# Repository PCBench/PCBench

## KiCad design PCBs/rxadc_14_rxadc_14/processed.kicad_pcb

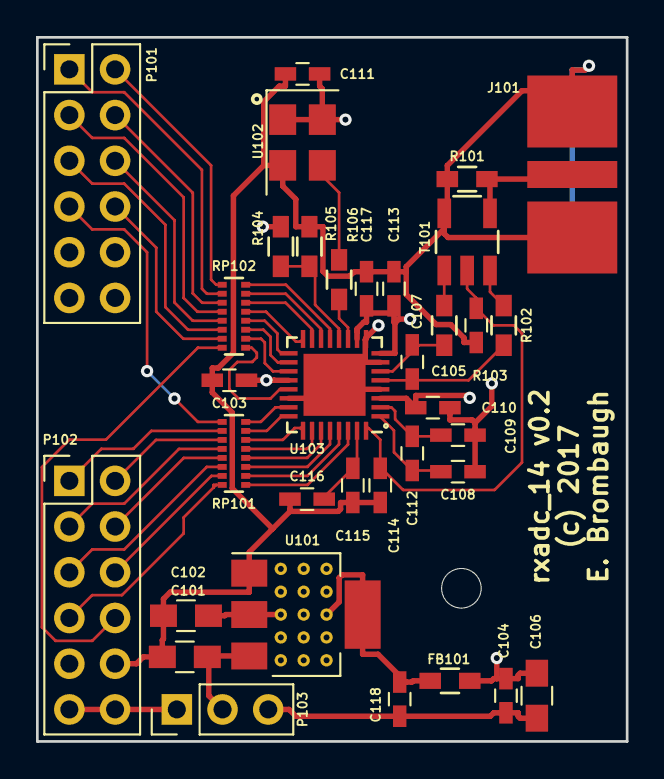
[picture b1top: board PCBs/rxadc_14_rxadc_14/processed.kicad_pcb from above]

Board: 4 copper layers, 32.8 x 39.1 mm, 35 parts (0 on the bottom side), 49 nets.

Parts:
C101, C102, C106: 10uf; C_0805_HandSoldering
C103, C104, C105, C108, C109, C110, C111, C113, C114, C115, C117, C118: 0.1uf; C_0603_HandSoldering
C107: 18pf; C_0603_HandSoldering
C112, C116: 1uf; C_0603_HandSoldering
FB101: FILTER; R_0603_HandSoldering
J101: SMA; SMA_END
P101, P102: CONN_02X06; Pin_Header_Straight_2x06_Pitch2.54mm
P103: CONN_01X03; Pin_Header_Straight_1x03_Pitch2.54mm
R101, R106: 50; R_0603_HandSoldering
R102, R103: 20; R_0603_HandSoldering
R104: 4k7; R_0603_HandSoldering
R105: 10k; R_0603_HandSoldering
RP101, RP102: 100; R_Array_EXB2HV
T101: TRANSFO4; Pulse_SMD_Balun
U101: LD1117S33CTR; SOT-223
U102: ASFL1-80.000MHZ-EC-T; Crystal_SMD_Abracon_ASFL1-4pin_5.0x3.2mm
U103: ADC14C105; QFN-32-1EP_5x5mm_Pitch0.5mm_extended_pad

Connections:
+3.3VADC: C104.1, C106.1, C110.1, C113.1, C117.1, FB101.2, R104.1, U103.3, U103.8, U103.10
+3V3: C102.1, C103.1, C111.1, C118.2, FB101.1, U101.2, U101.4, U102.1, U102.4, U103.20
+5V: C101.1, P103.2, U101.3
GND: C101.2, C102.2, C103.2, C104.2, C105.1, C106.2, C108.1, C109.1, C110.2, C111.2, C113.2, C114.1, C115.1, C116.1, C117.2, C118.1, J101.2, P101.9, P101.10, P102.9, P102.10, P103.3, R101.1, R105.2, T101.5, U101.1, U102.2, U103.4, U103.7, U103.9, U103.22, U103.33
unnamed: C105.2, C114.2, T101.2, U103.32
unnamed: C107.1, R102.2, U103.5
unnamed: C107.2, R103.2, U103.6
unnamed: C108.2, C112.1, U103.1
unnamed: C109.2, C112.2, U103.2
unnamed: C115.2, C116.2, U103.31
unnamed: J101.1, R101.2, T101.4
unnamed: P101.1, RP102.10
unnamed: P101.2, RP102.9
unnamed: P101.3, RP102.12
unnamed: P101.4, RP102.11
unnamed: P101.5, RP102.14
unnamed: P101.6, RP102.13
unnamed: P101.7, RP101.9
unnamed: P101.8, RP102.15
unnamed: P102.1, RP101.10
unnamed: P102.2, RP101.11
unnamed: P102.3, RP101.12
unnamed: P102.4, RP101.13
unnamed: P102.5, RP101.14
unnamed: P102.6, RP101.15
unnamed: P102.7, RP101.16
unnamed: P102.8, RP102.16
unnamed: P102.11, P102.12, P103.1
unnamed: R102.1, T101.3
unnamed: R103.1, T101.1
unnamed: R104.2, R105.1, U103.12
unnamed: R106.1, U103.11
unnamed: R106.2, U102.3
unnamed: RP101.1, U103.30
unnamed: RP101.2, U103.29
unnamed: RP101.3, U103.28
unnamed: RP101.4, U103.27
unnamed: RP101.5, U103.26
unnamed: RP101.6, U103.25
unnamed: RP101.7, U103.24
unnamed: RP101.8, U103.23
unnamed: RP102.1, U103.21
unnamed: RP102.2, U103.19
unnamed: RP102.3, U103.18
unnamed: RP102.4, U103.17
unnamed: RP102.5, U103.16
unnamed: RP102.6, U103.15
unnamed: RP102.7, U103.14
unnamed: RP102.8, U103.13

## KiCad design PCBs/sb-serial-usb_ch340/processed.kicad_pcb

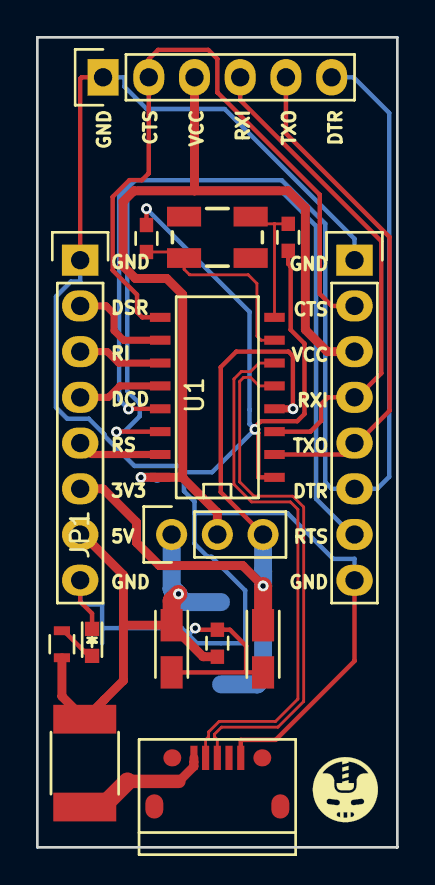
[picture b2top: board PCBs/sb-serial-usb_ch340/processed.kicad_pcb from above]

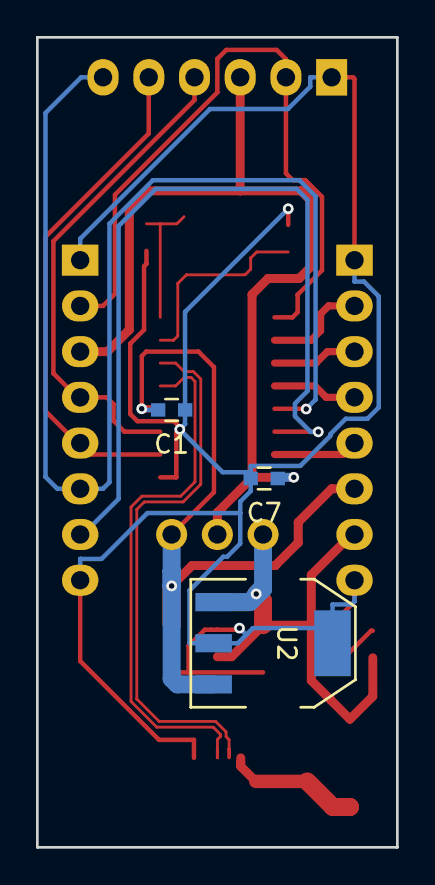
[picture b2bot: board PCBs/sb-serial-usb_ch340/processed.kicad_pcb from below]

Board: 2 copper layers, 20.0 x 45.0 mm, 18 parts (3 on the bottom side), 19 nets.

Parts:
C1: 10n; C_0603
C2, C3: 22p; C_0603
C4, C6: 10u 6V TANT; TantalC_SizeA_EIA-3216_Reflow
C5: 1u; C_0603
C7: 100n; C_0603
D1: BLUE; LED_0603
F1: 1.5A; R_1812
JP1: JUMPER3; Pin_Header_Straight_1x03
P1: CONN_01X06; Pin_Header_Straight_1x06
P2, P3: CONN_01X08; Pin_Header_Straight_1x08
P4: MINI-USB; USB_Micro-B
R1: 1K; R_0603
U1: CH340G; SO-16-N
U2: LDO MIC39100 3.3V; SOT-223
Y1: 12Mhz; CRYSTAL-SMD-5X3

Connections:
+5V: C4.1, C5.1, F1.2, JP1.1, P3.7, R1.2, U2.1
CTS: P1.2, P2.2, U1.9
D+: P4.3, U1.5
D-: P4.2, U1.6
DCD: P3.4, U1.12
DSR: P3.2, U1.10
DTR: P1.6, P2.6, U1.13
GND: C1.1, C2.2, C3.2, C4.2, C5.2, C6.2, C7.2, D1.1, P1.1, P2.1, P2.8, P3.1, P3.8, P4.5, U1.1, U2.2, U2.4
unnamed: C2.1, U1.7, Y1.1
unnamed: C3.1, U1.8, Y1.2
unnamed: D1.2, R1.1
unnamed: F1.1, P4.1
RI: P3.3, U1.11
RS232: P3.5, U1.15
RTS: P2.7, U1.14
RXI: P1.4, P2.4, U1.3
TXO: P1.5, P2.5, U1.2
V3: C1.2, C6.1, JP1.3, P3.6, U1.4, U2.3
VCC: C7.1, JP1.2, P1.3, P2.3, U1.16

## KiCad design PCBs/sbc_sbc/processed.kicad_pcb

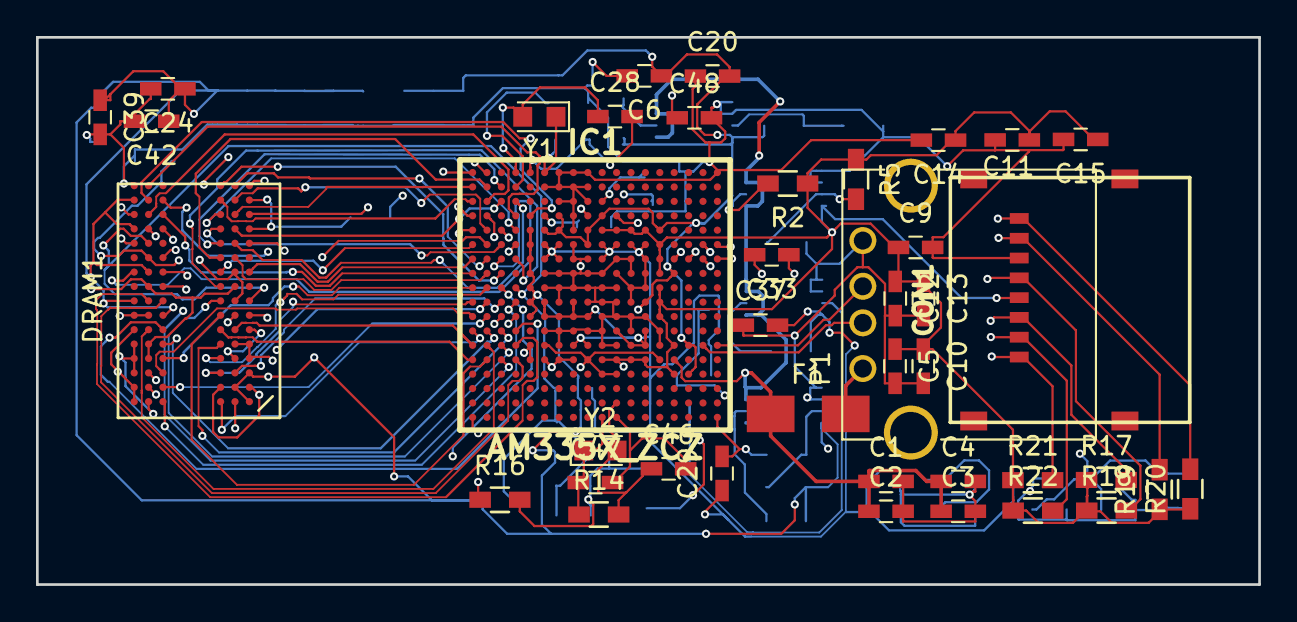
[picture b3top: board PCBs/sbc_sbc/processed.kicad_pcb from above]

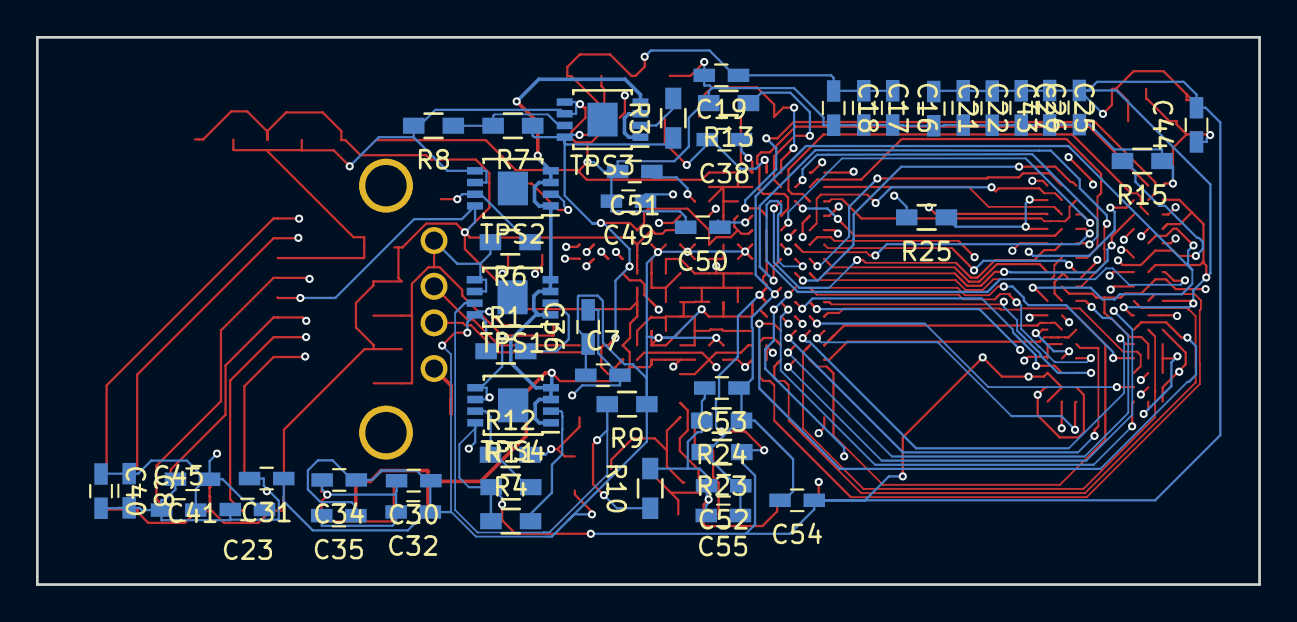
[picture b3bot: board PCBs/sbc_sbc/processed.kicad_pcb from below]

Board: 4 copper layers, 67.9 x 30.4 mm, 91 parts (50 on the bottom side), 85 nets.

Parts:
C1, C2, C3, C4, C15, C20, C26, C27, C37, C44, C45: 10uF; C_0603_HandSoldering
C5, C6, C7, C8: 22uF; C_0603_HandSoldering
C9, C10, C11, C12, C13, C14, C16, C17, C18, C19, C29, C30, C31, C32, C33, C34, C35, C36: 10nF; C_0603_HandSoldering
C21, C22, C23, C24, C25, C39, C40, C41, C42, C43, C48, C49, C50, C51: 1uF; C_0603_HandSoldering
C28, C38: 25pF; C_0603_HandSoldering
C46, C47: 24pF; C_0603_HandSoldering
C52, C53, C54, C55: 0.1uF; C_0603_HandSoldering
CON1: Micro_SD_Card; MICRO_SD_HINGE_AMP
DRAM1: DRAM-IS43TR16128B-125KBL; BGA-96_pitch0.8mm_dia0.4mm
F1: Polyfuse; Fuse_SMD1206_HandSoldering
IC1: AM335X_ZCZ; bga-csg324
P1: USB_A
R1, R2, R3, R4: 499K; R_0603_HandSoldering
R5: 250K; R_0603_HandSoldering
R6, R8, R10, R12: 80K; R_0603_HandSoldering
R7: 100K; R_0603_HandSoldering
R9: 30K; R_0603_HandSoldering
R11: 70K; R_0603_HandSoldering
R13, R17, R18, R19, R20, R21, R22, R25: 10K; R_0603_HandSoldering
R14: 1M; R_0603_HandSoldering
R15: 240; R_0603_HandSoldering
R16: 49.9; R_0603_HandSoldering
R23, R24: 1K; R_0603_HandSoldering
TPS1, TPS2, TPS3, TPS4: TPS82084; MSOP-8-1EP_3x3mm_Pitch0.65mm
Y1: 32.768KHz; Crystal_SMD_2012-2pin_2.0x1.2mm_HandSoldering
Y2: 24MHz; Crystal_SMD_2012-2pin_2.0x1.2mm_HandSoldering

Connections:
1.1V: C7.1, C29.1, C30.1, C31.1, C32.1, C33.1, C34.1, C35.1, C36.1, C37.2, IC1.A2, IC1.F6, IC1.F7, IC1.F10, IC1.F11, IC1.F12, IC1.F13, IC1.G6, IC1.G7, IC1.G10, IC1.G13, IC1.H11, IC1.H13, IC1.J12, IC1.J13, IC1.K6, IC1.K8, IC1.K12, IC1.L6, IC1.L7, IC1.L8, IC1.L9, IC1.M11, IC1.M13, IC1.N8, IC1.N9, IC1.N12, IC1.N13, R1.1, R9.1, TPS1.8
1.8V: C6.1, C16.1, C17.1, C18.1, C19.1, C20.2, IC1.D7, IC1.D10, IC1.E6, IC1.E7, IC1.E9, IC1.E14, IC1.F9, IC1.H15, IC1.K13, IC1.N6, IC1.N16, IC1.P9, IC1.P14, IC1.R10, IC1.R11, IC1.R16, R3.1, R7.1, TPS3.8
+1.5V: C8.1, C21.1, C22.1, C23.1, C24.1, C25.1, C26.1, C27.2, C39.1, C40.1, C41.1, C42.1, C43.1, C44.2, C45.2, C54.1, DRAM1.A1, DRAM1.A8, DRAM1.B2, DRAM1.C1, DRAM1.C9, DRAM1.D2, DRAM1.D9, DRAM1.E9, DRAM1.F1, DRAM1.G7, DRAM1.H2, DRAM1.H9, DRAM1.K2, DRAM1.K8, DRAM1.N1, DRAM1.N9, DRAM1.R1, DRAM1.R9, IC1.E5, IC1.F5, IC1.G5, IC1.H5, IC1.J5, IC1.K5, IC1.L5, R4.1, R11.1, R23.1, R25.1, TPS4.8
+3V3: C5.1, C9.1, C10.1, C11.1, C12.1, C13.1, C14.1, C15.1, CON1.4, IC1.E10, IC1.E11, IC1.E12, IC1.E13, IC1.F14, IC1.G14, IC1.H14, IC1.J14, IC1.K14, IC1.L14, IC1.N5, IC1.N15, IC1.P5, IC1.P6, IC1.P7, IC1.P8, IC1.P10, IC1.P11, IC1.P12, IC1.P13, IC1.R15, R2.1, R5.1, R17.1, R18.1, R19.1, R20.1, R21.1, R22.1, TPS2.8
+5V: C1.1, C2.1, C3.1, C4.1, F1.1, IC1.P15, TPS1.1, TPS1.3, TPS1.4, TPS2.1, TPS2.3, TPS2.4, TPS3.1, TPS3.3, TPS3.4, TPS4.1, TPS4.3, TPS4.4
/1.1FB: R9.2, R10.1, TPS1.7
/1.5FB: R11.2, R12.1, TPS4.7
/1.8FB: R7.2, R8.1, TPS3.7
/3.3FB: R5.2, R6.1, TPS2.7
/DDR_A0: DRAM1.N3, IC1.F3
/DDR_A1: DRAM1.P7, IC1.H1
/DDR_A2: DRAM1.P3, IC1.E4
/DDR_A3: DRAM1.N2, IC1.C3
/DDR_A4: DRAM1.P8, IC1.C2
/DDR_A5: DRAM1.P2, IC1.B1
/DDR_A6: DRAM1.R8, IC1.D5
/DDR_A7: DRAM1.R2, IC1.E2
/DDR_A8: DRAM1.T8, IC1.D4
/DDR_A9: DRAM1.R3, IC1.C1
/DDR_A10: DRAM1.L7, IC1.F4
/DDR_A11: DRAM1.R7, IC1.F2
/DDR_A12: DRAM1.N7, IC1.E3
/DDR_A13: DRAM1.T3, IC1.H3
/DDR_BA0: DRAM1.M2, IC1.C4
/DDR_BA1: DRAM1.N8, IC1.E1
/DDR_BA2: DRAM1.M3, IC1.B3
/DDR_CASn: DRAM1.K3, IC1.F1
/DDR_CK: DRAM1.J7, IC1.D2
/DDR_CKE: DRAM1.K9, IC1.G3
/DDR_CKn: DRAM1.K7, IC1.D1
/DDR_CSn0: DRAM1.L2, IC1.H2
/DDR_D0: DRAM1.E3, IC1.M3
/DDR_D1: DRAM1.F7, IC1.M4
/DDR_D2: DRAM1.F2, IC1.N1
/DDR_D3: DRAM1.F8, IC1.N2
/DDR_D4: DRAM1.H3, IC1.N3
/DDR_D5: DRAM1.H8, IC1.N4
/DDR_D6: DRAM1.G2, IC1.P3
/DDR_D7: DRAM1.H7, IC1.P4
/DDR_D8: DRAM1.D7, IC1.J1
/DDR_D9: DRAM1.C3, IC1.K1
/DDR_D10: DRAM1.C8, IC1.K2
/DDR_D11: DRAM1.C2, IC1.K3
/DDR_D12: DRAM1.A7, IC1.K4
/DDR_D13: DRAM1.A2, IC1.L3
/DDR_D14: DRAM1.B8, IC1.L4
/DDR_D15: DRAM1.A3, IC1.M1
/DDR_DQM0: DRAM1.E7, IC1.M2
/DDR_DQM1: DRAM1.D3, IC1.J2
/DDR_DQS0: DRAM1.F3, IC1.P1
/DDR_DQS1: DRAM1.C7, IC1.L1
/DDR_DQSn0: DRAM1.G3, IC1.P2
/DDR_DQSn1: DRAM1.B7, IC1.L2
/DDR_ODT: DRAM1.K1, IC1.G1
/DDR_RASn: DRAM1.J3, IC1.G4
/DDR_RESETn: DRAM1.T2, IC1.G2, R25.2
/DDR_VREF: C52.1, C53.1, C54.2, C55.1, DRAM1.H1, DRAM1.M8, IC1.J4, R23.2, R24.1
/DDR_WEn: DRAM1.L3, IC1.B2
/DDR_ZQ: DRAM1.L8, R15.2
/MMC0_CLK: CON1.5, IC1.G17, R18.2
/MMC0_CMD: CON1.3, IC1.G18, R17.2
/MMC0_DAT0: CON1.7, IC1.G16, R19.2
/MMC0_DAT1: CON1.8, IC1.G15, R20.2
/MMC0_DAT2: CON1.1, IC1.F18, R21.2
/MMC0_DAT3: CON1.2, IC1.F17, R22.2
/USBD+: IC1.N17, P1.2
/USBD-: IC1.N18, P1.3
GND: C1.2, C2.2, C3.2, C4.2, C5.2, C6.2, C7.2, C8.2, C9.2, C10.2, C11.2, C12.2, C13.2, C14.2, C15.2, C16.2, C17.2, C18.2, C19.2, C20.1, C21.2, C22.2, C23.2, C24.2, C25.2, C26.2, C27.1, C29.2, C30.2, C31.2, C32.2, C33.2, C34.2, C35.2, C36.2, C37.1, C39.2, C40.2, C41.2, C42.2, C43.2, C44.1, C45.1, C48.2, C49.2, C50.2, C51.2, C52.2, C53.2, C55.2, CON1.6, DRAM1.A9, DRAM1.B1, DRAM1.B3, DRAM1.B9, DRAM1.D1, DRAM1.D8, DRAM1.E1, DRAM1.E2, DRAM1.E8, DRAM1.F9, DRAM1.G1, DRAM1.G8, DRAM1.G9, DRAM1.J2, DRAM1.J8, DRAM1.M1, DRAM1.M9, DRAM1.P1, DRAM1.P9, DRAM1.T1, DRAM1.T9, IC1.A1, IC1.A7, IC1.A8, IC1.A9, IC1.A18, IC1.B6, IC1.B7, IC1.B8, IC1.B9, IC1.C7, IC1.C8, IC1.C9, IC1.D8, IC1.E8, IC1.F8, IC1.G8, IC1.G9, IC1.G11, IC1.G12, IC1.H6, IC1.H7, IC1.H8, IC1.H9, IC1.H10, IC1.H12, IC1.J6, IC1.J7, IC1.J8, IC1.J9, IC1.J10, IC1.J11, IC1.K7, IC1.K9, IC1.K10, IC1.K11, IC1.L10, IC1.L11, IC1.L12, IC1.L13, IC1.M6, IC1.M7, IC1.M8, IC1.M9, IC1.M10, IC1.M12, IC1.M14, IC1.N7, IC1.N10, IC1.N11, IC1.N14, IC1.V1, IC1.V18, P1.4, R6.2, R8.2, R10.2, R12.2, R13.2, R15.1, R16.2, R24.2, TPS1.5, TPS1.6, TPS2.5, TPS2.6, TPS3.5, TPS3.6, TPS4.5, TPS4.6
GND_OSC0: C46.2, C47.2, IC1.V11
GND_OSC1: C28.2, C38.2, IC1.A5
unnamed: C28.1, IC1.A4, Y1.2
unnamed: C38.1, IC1.A6, Y1.1
unnamed: C46.1, IC1.U11, R14.2, Y2.2
unnamed: C47.1, IC1.V10, R14.1, Y2.1
unnamed: C48.1, IC1.D11
unnamed: C49.1, IC1.D9
unnamed: C50.1, IC1.D6
unnamed: C51.1, IC1.C10
unnamed: F1.2, P1.1
unnamed: IC1.B4, R13.1
unnamed: IC1.J3, R16.1
unnamed: R1.2, TPS1.2
unnamed: R2.2, TPS2.2
unnamed: R3.2, TPS3.2
unnamed: R4.2, TPS4.2

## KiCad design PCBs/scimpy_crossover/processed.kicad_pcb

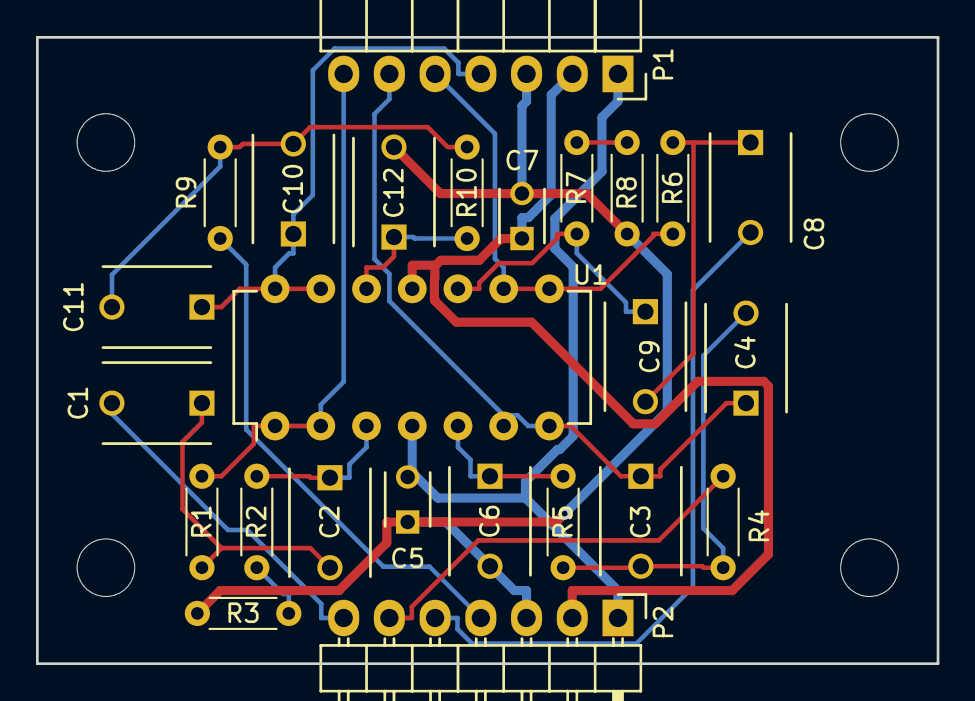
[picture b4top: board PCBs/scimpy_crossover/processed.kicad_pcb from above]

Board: 2 copper layers, 50.0 x 34.8 mm, 29 parts (0 on the bottom side), 21 nets.

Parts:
C1, C2, C3, C4, C6, C8, C9, C10, C11, C12: 100n; C_Disc_D6_P5
C5, C7: 100n; C_Disc_D3_P2.5
P1: CONN_01X07; Socket_Strip_Angled_1x07
P2: CONN_01X07; Pin_Header_Angled_1x07
R1, R2, R3, R4, R5, R6, R7, R8, R9, R10: R; R_Axial_DIN0204_L3.6mm_D1.6mm_P5.08mm_Horizontal
U1: TL074; DIP-14_W7.62mm
mnt1, mnt2, mnt3, mnt4: MountingHole_3.2mm_M3

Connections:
+15V: C5.2, P1.1, P2.1, U1.4
-15V: C7.1, P1.2, P2.2, U1.11
/left_high_out: P1.5, R6.2, U1.8, U1.9
/left_low_out: C10.1, C11.1, P1.4, U1.13, U1.14
/left_tweeter_ph: C8.2, P2.5
/left_woofer_in: P2.4, R9.1
/right_high_out: P1.7, R1.2, U1.1, U1.2
/right_low_out: C3.1, C4.1, P1.6, U1.6, U1.7
/right_tweeter_ph: C1.2, P2.7
/right_woofer_in: P2.6, R4.1
GND: C5.1, C6.2, C7.2, C12.2, P1.3, P2.3, R3.1, R8.1
unnamed: C1.1, C2.2, R1.1
unnamed: C2.1, R2.2, U1.3
unnamed: C3.2, C4.2, R4.2, R5.2
unnamed: C6.1, R5.1, U1.5
unnamed: C8.1, C9.2, R6.1
unnamed: C9.1, R7.2, U1.10
unnamed: C10.2, C11.2, R9.2, R10.2
unnamed: C12.1, R10.1, U1.12
unnamed: R2.1, R3.2
unnamed: R7.1, R8.2

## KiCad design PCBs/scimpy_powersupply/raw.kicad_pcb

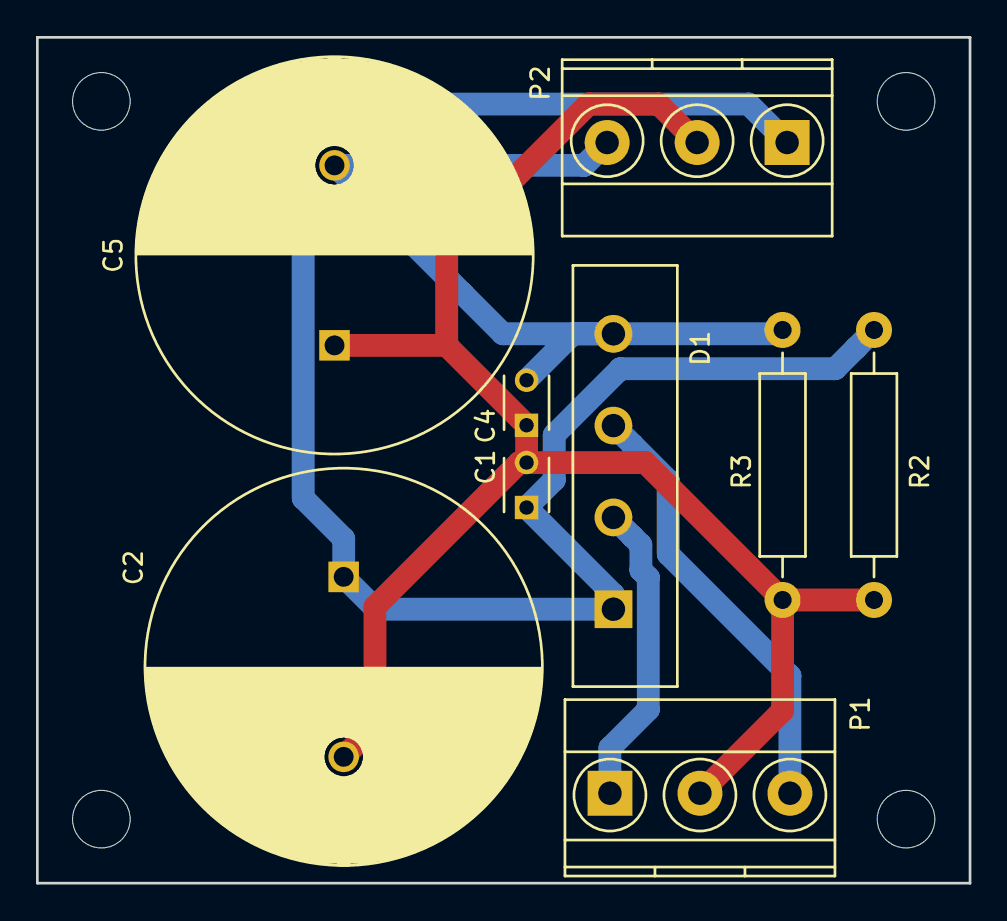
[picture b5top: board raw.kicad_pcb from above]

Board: 2 copper layers, 51.8 x 47.0 mm, 9 parts (0 on the bottom side), 5 nets.

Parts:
C1, C4: 100n; C_Disc_D3_P2.5
C2, C5: 6800u; C_Radial_D22_L41_P10
D1: Diode_Bridge; Diode_Bridge_18.5x5.5
P1, P2: CONN_01X03; TerminalBlock_Pheonix_MKDS1.5-3pol
R2, R3: 1K 1W; Resistor_Horizontal_RM15mm

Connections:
+15V: C1.1, C2.1, D1.3, P2.1, R2.1
-15V: C4.2, C5.2, D1.1, P2.3, R3.2
/+12VAC: D1.4, P1.3
/-12VAC: D1.2, P1.1
GND: C1.2, C2.2, C4.1, C5.1, P1.2, P2.2, R2.2, R3.1

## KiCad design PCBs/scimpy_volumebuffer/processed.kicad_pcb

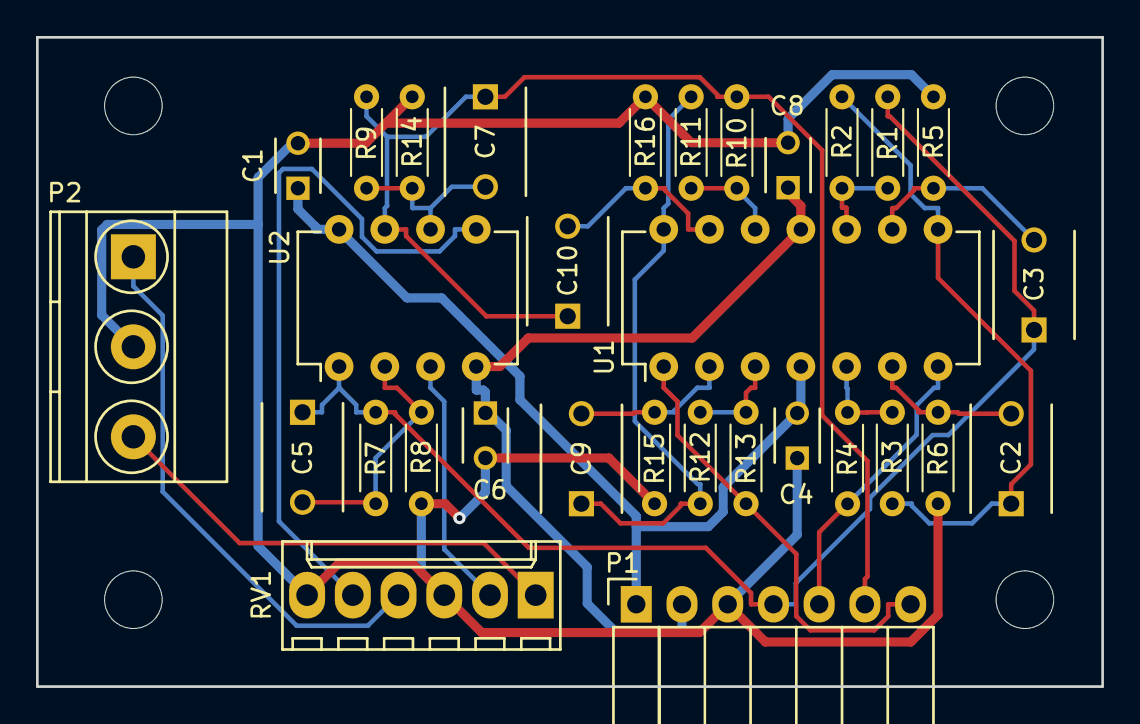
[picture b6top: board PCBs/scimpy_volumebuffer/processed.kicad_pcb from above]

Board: 2 copper layers, 59.2 x 36.1 mm, 34 parts (0 on the bottom side), 23 nets.

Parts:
C1, C4, C6, C8: 100n; C_Disc_D3_P2.5
C2, C3, C5, C7, C9, C10: 100n; C_Disc_D6_P5
P1: CONN_01X07; Socket_Strip_Angled_1x07
P2: CONN_01X03; TerminalBlock_Pheonix_MKDS1.5-3pol
R1, R2, R3, R4, R10, R11, R12, R13: 2K2; R_Axial_DIN0204_L3.6mm_D1.6mm_P5.08mm_Horizontal
R5, R6, R15, R16: Rph; R_Axial_DIN0204_L3.6mm_D1.6mm_P5.08mm_Horizontal
R7, R9: Rbs1; R_Axial_DIN0204_L3.6mm_D1.6mm_P5.08mm_Horizontal
R8, R14: Rbs2; R_Axial_DIN0204_L3.6mm_D1.6mm_P5.08mm_Horizontal
RV1: DUAL_POT; Molex_KK-6410-06_06x2.54mm_Straight
U1: TL074; DIP-14_W7.62mm
U2: TL072; DIP-8_W7.62mm
mnt1, mnt2, mnt3: MountingHole_3.2mm_M3

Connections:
+15V: C1.1, C4.2, P1.1, U1.4, U2.8
-15V: C6.1, C8.1, P1.2, U1.11, U2.4
/left_bass: C3.1, C5.1, P1.4, R1.2, R7.2, U2.1
/left_in: P2.1, RV1.4
/left_tweet: P1.5, R4.1, U1.7
/right_bass: C7.1, C10.1, P1.6, R9.2, R10.2, U2.7
/right_in: P2.3, RV1.1
/right_tweet: P1.7, R13.1, U1.1
GND: C1.2, C4.1, C6.2, C8.2, P1.3, P2.2, R5.1, R6.1, R8.2, R14.1, R15.1, R16.1, RV1.3, RV1.6
unnamed: C2.1, R2.1, R3.2, U1.8
unnamed: C2.2, R6.2, U1.6
unnamed: C3.2, R5.2, U1.9
unnamed: C5.2, R7.1, R8.1, U2.2
unnamed: C7.2, R9.1, R14.2, U2.6
unnamed: C9.1, R11.1, R12.2, U1.14
unnamed: C9.2, R15.2, U1.2
unnamed: C10.2, R16.2, U1.13
unnamed: R1.1, R2.2, U1.10
unnamed: R3.1, R4.2, U1.5
unnamed: R10.1, R11.2, U1.12
unnamed: R12.1, R13.2, U1.3
unnamed: RV1.2, U2.3
unnamed: RV1.5, U2.5

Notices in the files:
PCBs/rxadc_14_rxadc_14/processed.kicad_pcb:
(c) 2017
